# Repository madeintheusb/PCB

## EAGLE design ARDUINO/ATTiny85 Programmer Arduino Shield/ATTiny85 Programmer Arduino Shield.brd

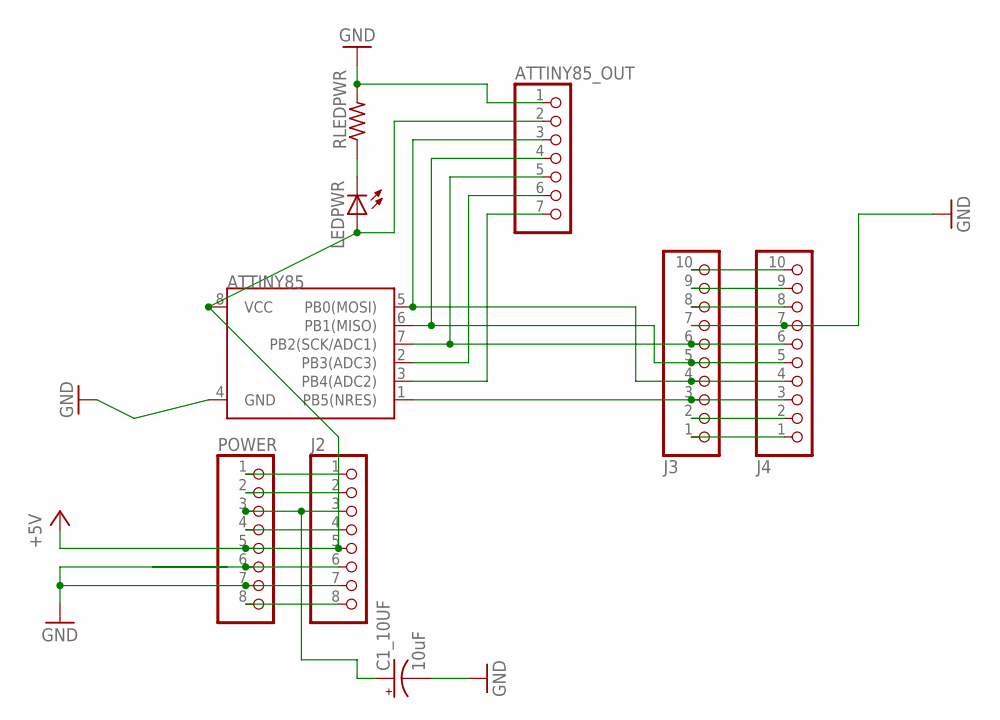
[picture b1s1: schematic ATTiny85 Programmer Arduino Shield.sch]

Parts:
ATTINY85: TINY85-20-DIP; DIP08
ATTINY85_OUT: PINHD-1X7; 1X07
C1_10UF: 10uF; EIA3216
J2: PINHD-1X8TH; 1X08-TH
J3, J4: PINHD-1X10TH; 1X10-TH
LEDPWR: LEDCHIPLED_0805; CHIPLED_0805
POWER: PINHD-1X8TH; 1X08-TH
RLEDPWR: R-US_R0805; R0805

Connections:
+5V: ATTINY85.8 (VCC), ATTINY85_OUT.2, J2.5, LEDPWR.A, POWER.5
+9V: J2.8, POWER.8
GND: ATTINY85.4 (GND), ATTINY85_OUT.1, C1_10UF.C (-), J2.7, J3.7, J4.7, POWER.7, RLEDPWR.2
unnamed: ATTINY85.7 (PB2(SCK/ADC1)), ATTINY85_OUT.5, J3.6, J4.6
unnamed: J3.1, J4.1
unnamed: ATTINY85.5 (PB0(MOSI)), ATTINY85_OUT.3, J3.4, J4.4
unnamed: ATTINY85.6 (PB1(MISO)), ATTINY85_OUT.4, J3.5, J4.5
unnamed: LEDPWR.C, RLEDPWR.1
unnamed: J3.2, J4.2
unnamed: ATTINY85.1 (PB5(NRES)), J3.3, J4.3
unnamed: ATTINY85.2 (PB3(ADC3)), ATTINY85_OUT.6
unnamed: ATTINY85.3 (PB4(ADC2)), ATTINY85_OUT.7
unnamed: J2.6, POWER.6
unnamed: J2.2, POWER.2
unnamed: J2.1, POWER.1
unnamed: J3.9, J4.9
unnamed: J3.10, J4.10
unnamed: J3.8, J4.8
unnamed: J2.4, POWER.4
RESET: C1_10UF.A (+), J2.3, POWER.3

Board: 2 copper layers, 9 parts (0 on the bottom side), 20 nets, no tracks yet.

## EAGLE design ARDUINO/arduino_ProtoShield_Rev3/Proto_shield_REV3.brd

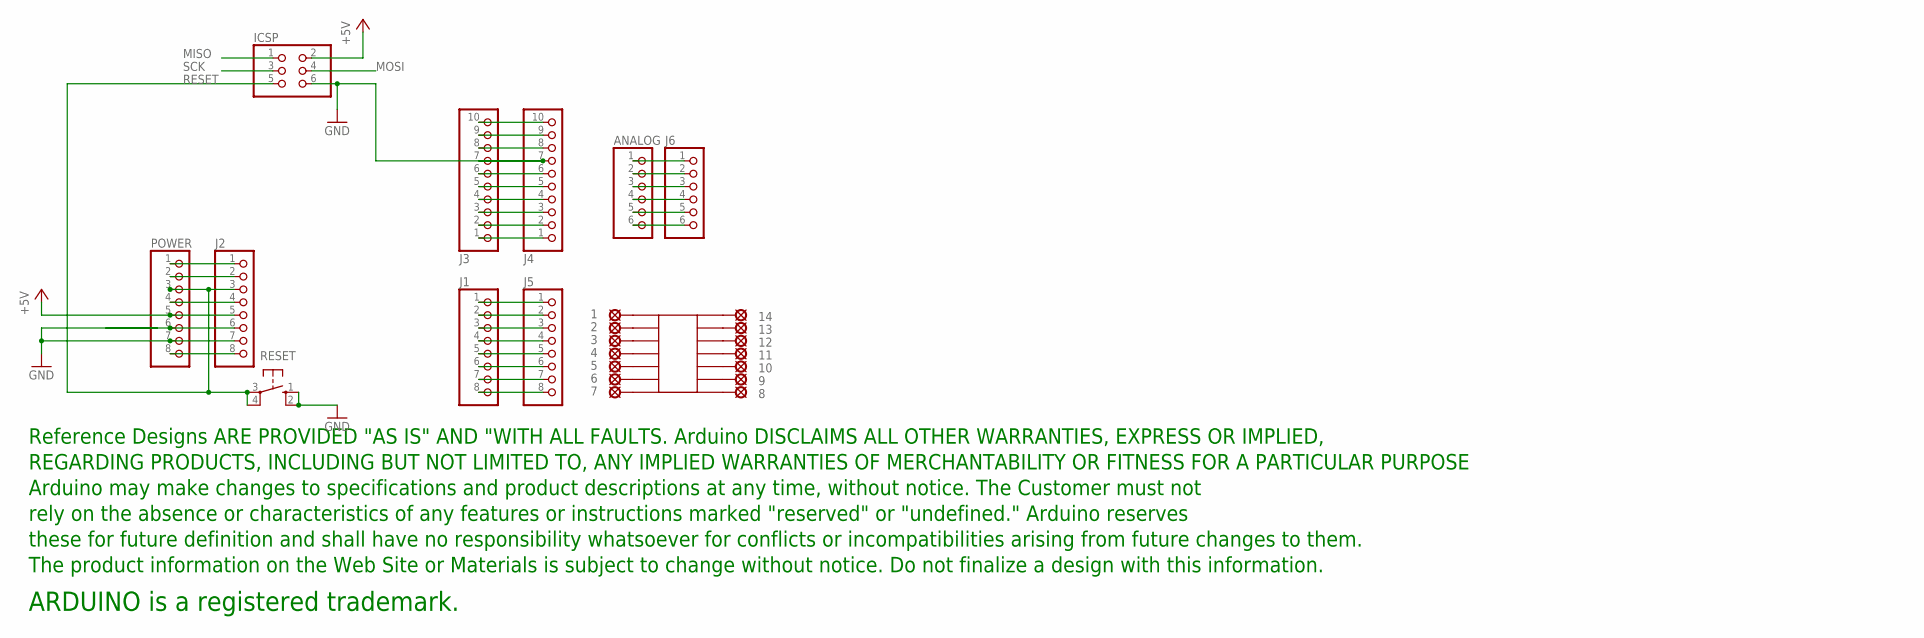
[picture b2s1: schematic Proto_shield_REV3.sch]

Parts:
1, 2, 3, 4, 5, 6, 7, 8, 9, 10, 11, 12, 13, 14: LSP10
ANALOG: PINHD-1X6; 1X06
IC2: SMD-14; SO-14NMW
ICSP: PINHD-2X3; 2X03
J1, J2, J5: PINHD-1X8TH; 1X08-TH
J3, J4: PINHD-1X10TH; 1X10-TH
J6: PINHD-1X6; 1X06
POWER: PINHD-1X8TH; 1X08-TH
RESET: 10-XX; B3F-10XX
U$1: DISCLAIMER

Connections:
+5V: ICSP.2, J2.5, POWER.5
+9V: J2.8, POWER.8
GND: ICSP.6, J2.7, J3.7, J4.7, POWER.7, RESET.1 (S), RESET.2 (S1)
MISO: ICSP.1
MOSI: ICSP.4
unnamed: J3.6, J4.6
unnamed: J3.1, J4.1
unnamed: J3.4, J4.4
unnamed: J3.5, J4.5
unnamed: J3.2, J4.2
unnamed: J3.3, J4.3
unnamed: J1.1, J5.1
unnamed: J1.2, J5.2
unnamed: J1.3, J5.3
unnamed: J1.4, J5.4
unnamed: J1.5, J5.5
unnamed: J1.6, J5.6
unnamed: J1.7, J5.7
unnamed: J1.8, J5.8
unnamed: ANALOG.1, J6.1
unnamed: ANALOG.2, J6.2
unnamed: ANALOG.3, J6.3
unnamed: ANALOG.4, J6.4
unnamed: ANALOG.5, J6.5
unnamed: ANALOG.6, J6.6
unnamed: 14.MP, IC2.P$14
unnamed: J2.6, POWER.6
unnamed: J2.2, POWER.2
unnamed: J2.1, POWER.1
unnamed: 13.MP, IC2.P$13
unnamed: 12.MP, IC2.P$12
unnamed: 11.MP, IC2.P$11
unnamed: 10.MP, IC2.P$10
unnamed: 9.MP, IC2.P$9
unnamed: 8.MP, IC2.P$8
unnamed: 7.MP, IC2.P$7
unnamed: 6.MP, IC2.P$6
unnamed: 5.MP, IC2.P$5
unnamed: 3.MP, IC2.P$3
unnamed: 2.MP, IC2.P$2
unnamed: 1.MP, IC2.P$1
unnamed: 4.MP, IC2.P$4
unnamed: J3.9, J4.9
unnamed: J3.10, J4.10
unnamed: J3.8, J4.8
unnamed: J2.4, POWER.4
RESET: ICSP.5, J2.3, POWER.3, RESET.3, RESET.4 (P1)
SCK: ICSP.3

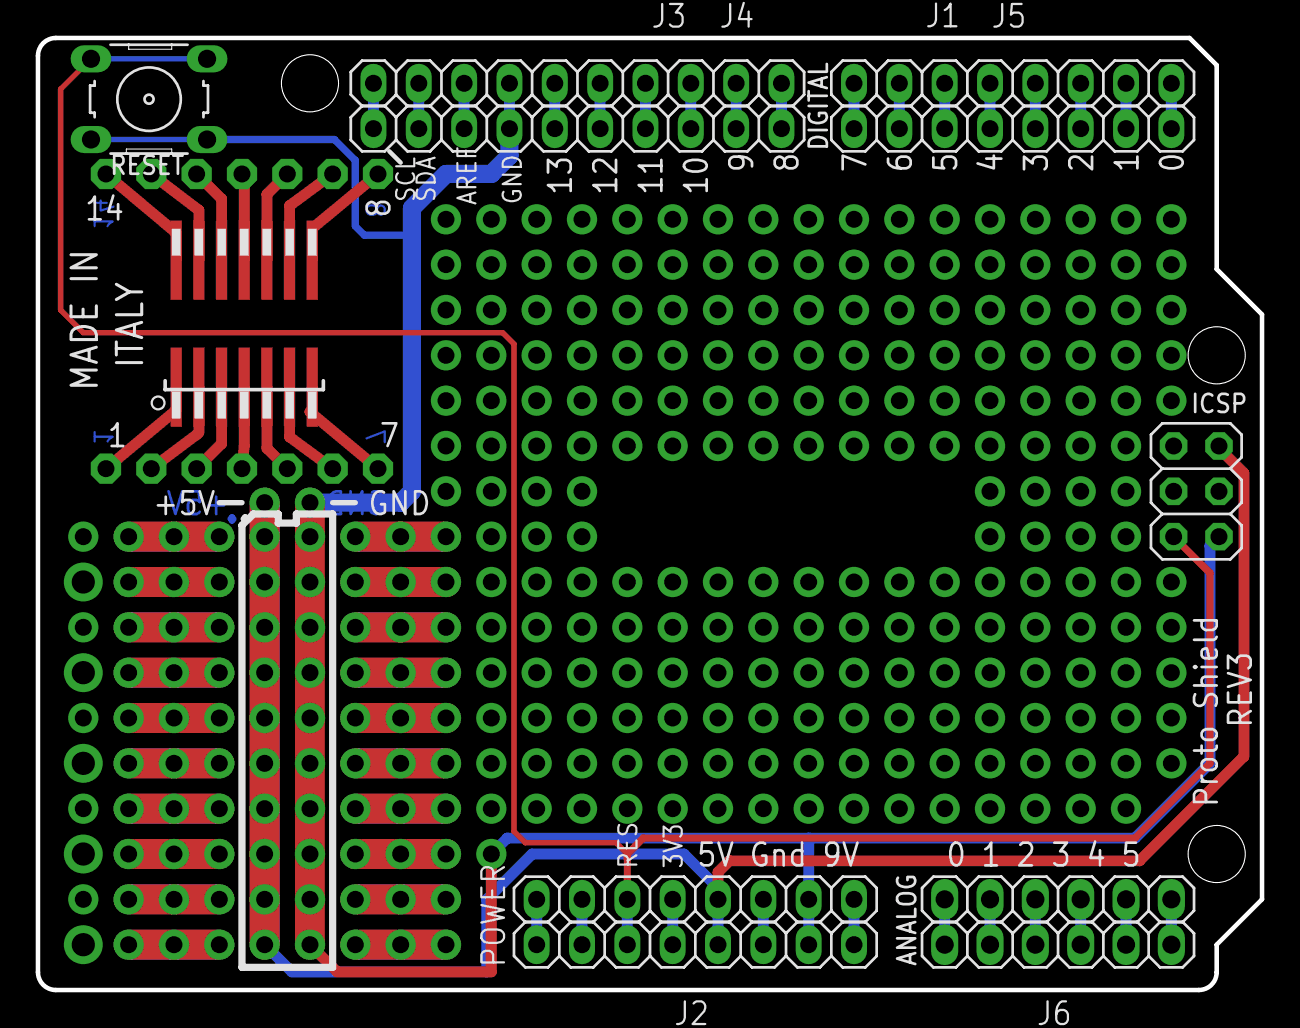
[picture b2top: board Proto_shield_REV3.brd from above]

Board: 2 copper layers, 68.6 x 53.3 mm, 26 parts (0 on the bottom side), 45 nets.

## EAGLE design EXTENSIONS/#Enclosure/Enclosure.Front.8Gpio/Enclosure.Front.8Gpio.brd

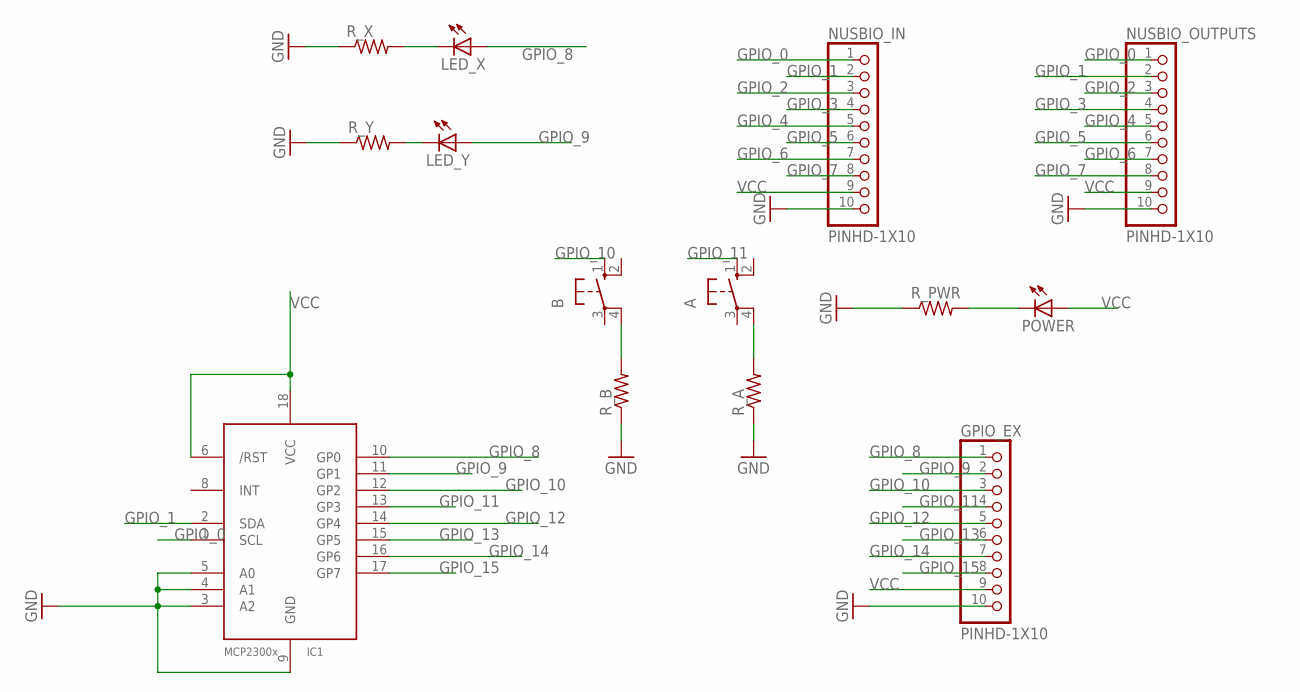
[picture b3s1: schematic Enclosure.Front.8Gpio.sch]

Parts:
A: 10-XX; B3F-10XX
B: 10-XX; B3F-10XX
GPIO_EX: PINHD-1X10; 1X10-BIG
IC1: MCP23008/SO; SO18W
LED_X: LEDSMT1206; 1206
LED_Y: LEDSMT1206; 1206
NUSBIO_IN: PINHD-1X10; 1X10-BIG
NUSBIO_OUTPUTS: PINHD-1X10; 1X10-BIG
POWER: LEDSMT1206; 1206
R_A: R-US_R1206; R1206
R_B: R-US_R1206; R1206
R_PWR: R-US_R1206; R1206
R_X: R-US_R1206; R1206
R_Y: R-US_R1206; R1206

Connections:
GND: GPIO_EX.10, IC1.3 (A2), IC1.4 (A1), IC1.5 (A0), IC1.9 (GND), NUSBIO_IN.10, NUSBIO_OUTPUTS.10, R_A.1, R_B.1, R_PWR.1, R_X.1, R_Y.1
GPIO_0: IC1.1 (SCL), NUSBIO_IN.1, NUSBIO_OUTPUTS.1
GPIO_1: IC1.2 (SDA), NUSBIO_IN.2, NUSBIO_OUTPUTS.2
GPIO_2: NUSBIO_IN.3, NUSBIO_OUTPUTS.3
GPIO_3: NUSBIO_IN.4, NUSBIO_OUTPUTS.4
GPIO_4: NUSBIO_IN.5, NUSBIO_OUTPUTS.5
GPIO_5: NUSBIO_IN.6, NUSBIO_OUTPUTS.6
GPIO_6: NUSBIO_IN.7, NUSBIO_OUTPUTS.7
GPIO_7: NUSBIO_IN.8, NUSBIO_OUTPUTS.8
GPIO_8: GPIO_EX.1, IC1.10 (GP0), LED_X.A
GPIO_9: GPIO_EX.2, IC1.11 (GP1), LED_Y.A
GPIO_10: B.1 (S), GPIO_EX.3, IC1.12 (GP2)
GPIO_11: A.1 (S), GPIO_EX.4, IC1.13 (GP3)
GPIO_12: GPIO_EX.5, IC1.14 (GP4)
GPIO_13: GPIO_EX.6, IC1.15 (GP5)
GPIO_14: GPIO_EX.7, IC1.16 (GP6)
GPIO_15: GPIO_EX.8, IC1.17 (GP7)
unnamed: POWER.C, R_PWR.2
unnamed: A.4 (P1), R_A.2
unnamed: B.4 (P1), R_B.2
unnamed: LED_X.C, R_X.2
unnamed: LED_Y.C, R_Y.2
VCC: GPIO_EX.9, IC1.6 (/RST), IC1.18 (VCC), NUSBIO_IN.9, NUSBIO_OUTPUTS.9, POWER.A

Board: 2 copper layers, 14 parts (6 on the bottom side), 23 nets, no tracks yet.

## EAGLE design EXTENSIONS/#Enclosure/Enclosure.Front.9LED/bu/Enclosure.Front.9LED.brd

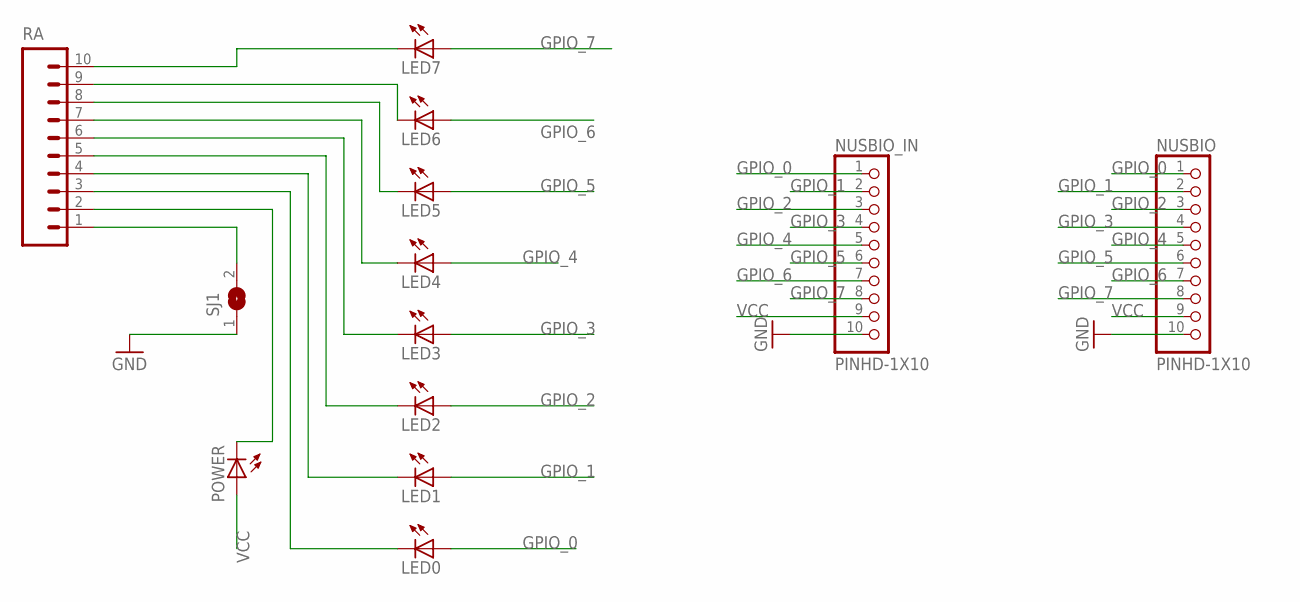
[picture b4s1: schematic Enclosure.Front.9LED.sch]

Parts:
LED0, LED1, LED2, LED3, LED4, LED5, LED6, LED7: LEDSMT1206; 1206
NUSBIO: PINHD-1X10; 1X10-BIG
NUSBIO_IN: PINHD-1X10; 1X10-BIG
POWER: LEDSMT1206; 1206
RA: M10SMD_MALE; 1X10_SMD_MALE
SJ1: SOLDERJUMPERREFLOW_NOPASTE; SOLDERJUMPER_REFLOW_NOPASTE

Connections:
GND: NUSBIO.10, NUSBIO_IN.10, SJ1.1
GPIO_0: LED0.A, NUSBIO.1, NUSBIO_IN.1
GPIO_1: LED1.A, NUSBIO.2, NUSBIO_IN.2
GPIO_2: LED2.A, NUSBIO.3, NUSBIO_IN.3
GPIO_3: LED3.A, NUSBIO.4, NUSBIO_IN.4
GPIO_4: LED4.A, NUSBIO.5, NUSBIO_IN.5
GPIO_5: LED5.A, NUSBIO.6, NUSBIO_IN.6
GPIO_6: LED6.A, NUSBIO.7, NUSBIO_IN.7
GPIO_7: LED7.A, NUSBIO.8, NUSBIO_IN.8
unnamed: POWER.C, RA.2
unnamed: RA.1, SJ1.2
unnamed: LED7.C, RA.10
unnamed: LED6.C, RA.9
unnamed: LED5.C, RA.8
unnamed: LED4.C, RA.7
unnamed: LED3.C, RA.6
unnamed: LED2.C, RA.5
unnamed: LED1.C, RA.4
unnamed: LED0.C, RA.3
VCC: NUSBIO.9, NUSBIO_IN.9, POWER.A

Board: 2 copper layers, 13 parts (2 on the bottom side), 20 nets, no tracks yet.

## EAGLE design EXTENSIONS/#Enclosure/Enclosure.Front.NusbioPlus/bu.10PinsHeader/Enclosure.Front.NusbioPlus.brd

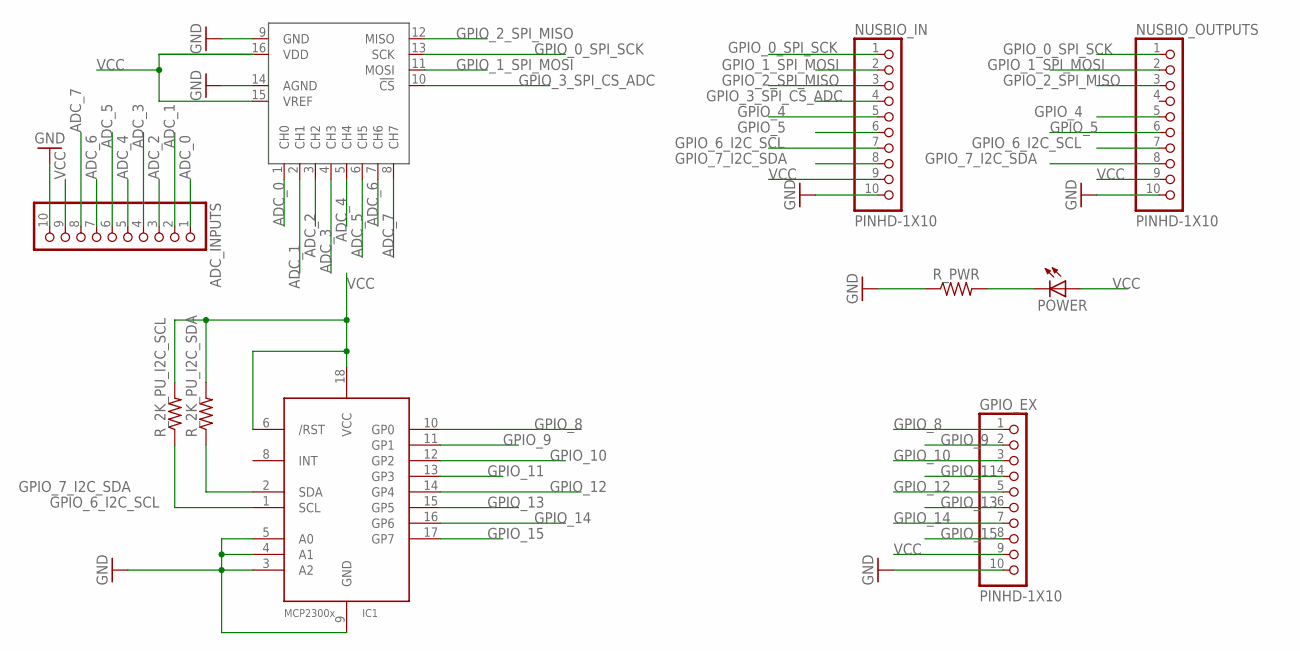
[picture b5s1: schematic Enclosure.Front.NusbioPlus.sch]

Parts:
ADC_INPUTS: PINHD-1X10; 1X10-BIG
GPIO_EX: PINHD-1X10; 1X10-BIG
IC1: MCP23008/SO; SO18W
NUSBIO_IN: PINHD-1X10; 1X10-BIG
NUSBIO_OUTPUTS: PINHD-1X10; 1X10-BIG
POWER: LEDSMT1206; 1206
R_2K_PU_I2C_SCL, R_2K_PU_I2C_SDA: R-US_R1206; R1206
R_PWR: R-US_R1206; R1206
U$1: MCP3008SL; SO16

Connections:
ADC_0: ADC_INPUTS.1, U$1.1 (CH0)
ADC_1: ADC_INPUTS.2, U$1.2 (CH1)
ADC_2: ADC_INPUTS.3, U$1.3 (CH2)
ADC_3: ADC_INPUTS.4, U$1.4 (CH3)
ADC_4: ADC_INPUTS.5, U$1.5 (CH4)
ADC_5: ADC_INPUTS.6, U$1.6 (CH5)
ADC_6: ADC_INPUTS.7, U$1.7 (CH6)
ADC_7: ADC_INPUTS.8, U$1.8 (CH7)
GND: ADC_INPUTS.10, GPIO_EX.10, IC1.3 (A2), IC1.4 (A1), IC1.5 (A0), IC1.9 (GND), NUSBIO_IN.10, NUSBIO_OUTPUTS.10, R_PWR.1, U$1.9 (GND), U$1.14 (AGND)
GPIO_0_SPI_SCK: NUSBIO_IN.1, NUSBIO_OUTPUTS.1, U$1.13 (SCK)
GPIO_1_SPI_MOSI: NUSBIO_IN.2, NUSBIO_OUTPUTS.2, U$1.11 (MOSI)
GPIO_2_SPI_MISO: NUSBIO_IN.3, NUSBIO_OUTPUTS.3, U$1.12 (MISO)
GPIO_3_SPI_CS_ADC: NUSBIO_IN.4, U$1.10 (!CS)
GPIO_4: NUSBIO_IN.5, NUSBIO_OUTPUTS.5
GPIO_5: NUSBIO_IN.6, NUSBIO_OUTPUTS.6
GPIO_6_I2C_SCL: IC1.1 (SCL), NUSBIO_IN.7, NUSBIO_OUTPUTS.7, R_2K_PU_I2C_SCL.1
GPIO_7_I2C_SDA: IC1.2 (SDA), NUSBIO_IN.8, NUSBIO_OUTPUTS.8, R_2K_PU_I2C_SDA.1
GPIO_8: GPIO_EX.1, IC1.10 (GP0)
GPIO_9: GPIO_EX.2, IC1.11 (GP1)
GPIO_10: GPIO_EX.3, IC1.12 (GP2)
GPIO_11: GPIO_EX.4, IC1.13 (GP3)
GPIO_12: GPIO_EX.5, IC1.14 (GP4)
GPIO_13: GPIO_EX.6, IC1.15 (GP5)
GPIO_14: GPIO_EX.7, IC1.16 (GP6)
GPIO_15: GPIO_EX.8, IC1.17 (GP7)
unnamed: POWER.C, R_PWR.2
VCC: ADC_INPUTS.9, GPIO_EX.9, IC1.6 (/RST), IC1.18 (VCC), NUSBIO_IN.9, NUSBIO_OUTPUTS.9, POWER.A, R_2K_PU_I2C_SCL.2, R_2K_PU_I2C_SDA.2, U$1.15 (VREF), U$1.16 (VDD)

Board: 2 copper layers, 10 parts (5 on the bottom side), 27 nets, no tracks yet.

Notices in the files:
parts and their libraries:
SparkFun-DigitalIC: Licensing: Creative Commons ShareAlike 4.0 International - https://creativecommons.org/licenses/by-sa/4.0
microbuilder: This work is placed in the public domain, and may be freely used for commercial and non-commercial work with the following conditions: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
